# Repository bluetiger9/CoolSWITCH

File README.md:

# CoolSWITCH

**Project structure**
- CoolSWITH-Kicad - Kicad project: schematics + PCB
- CoolSwitch - Arduino project
- Smashing-Dashboard - Smashing demo dashboard
- MQTT-Grafana - Grafana demo dashboard
- coolSwitchClient.py - secure HTTP client
 
**License**: 
- code: MIT
- kicad design: CC BY-NC-SA

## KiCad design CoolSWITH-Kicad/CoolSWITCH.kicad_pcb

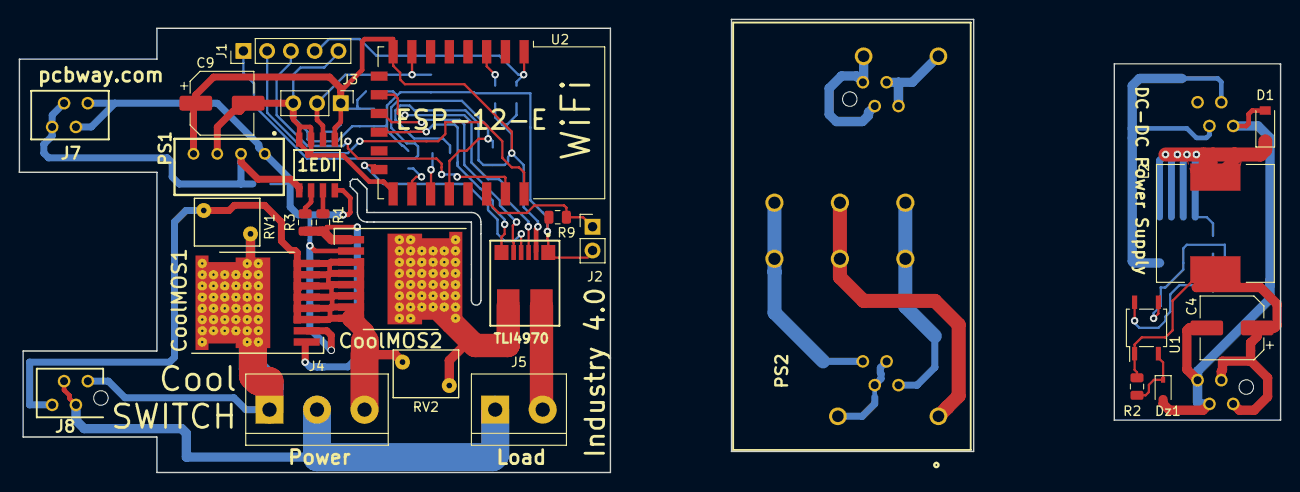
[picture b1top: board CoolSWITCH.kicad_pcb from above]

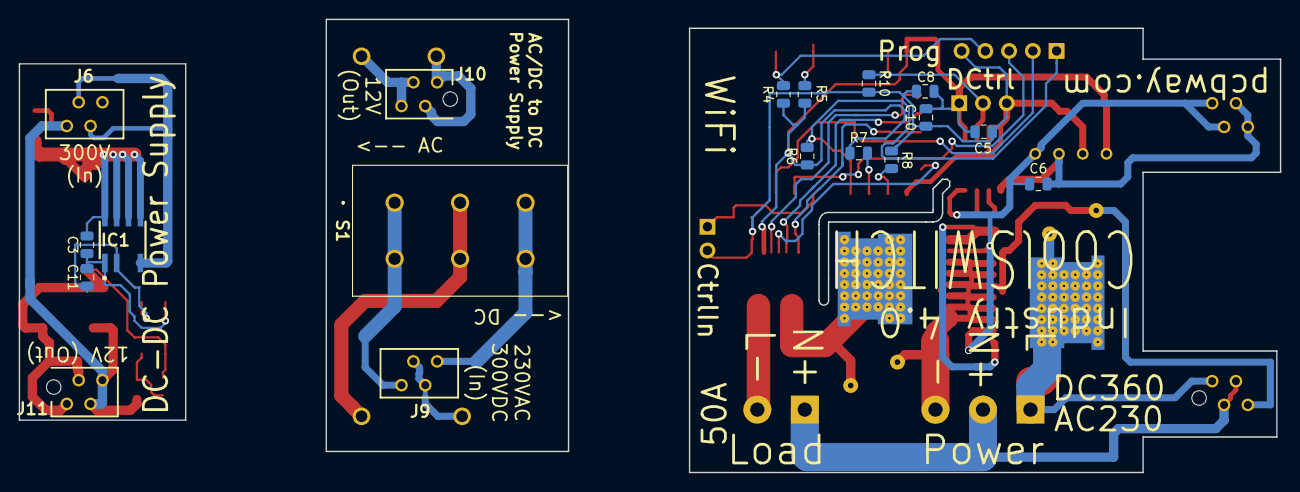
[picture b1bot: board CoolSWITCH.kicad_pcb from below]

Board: 2 copper layers, 134.9 x 48.5 mm, 44 parts (18 on the bottom side), 38 nets.

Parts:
1EDI: 1EDI20I12MFXUMA1; SOIC127P600X175-8N
C3: 0.1uF (25V); C_0805_2012Metric
C4: 220uF (16V); CP_Elec_6.3x7.7
C5, C8, C10: 100n; C_0805_2012Metric
C6: 1uF; C_0805_2012Metric
C9: 100u; CP_Elec_6.3x5.4
C11: 1nF (25V); C_0805_2012Metric
CoolMOS1, CoolMOS2: IPT60R028G7; Infineon_PG-HSOF-8-1_ThermalVias_fixed
D1: CD1408; D_SOD-123
Dz1: 11V; D_SOD-323
IC1: LNK3206D-TL; LNK3206D
J1: Prog; PinHeader_1x05_P2.54mm_Vertical
J2: CTRL_IN; PinHeader_1x02_P2.54mm_Vertical
J3: Direct_Ctrl; PinHeader_1x03_P2.54mm_Vertical
J4: POWER; TerminalBlock_bornier-3_P5.08mm
J5: LOAD; TerminalBlock_bornier-2_P5.08mm
J6, J9: PS_DC_IN; MicroMatch-215464-4
J7: PS_OUT; MicroMatch-215464-4
J8: PS_IN; MicroMatch-7-215079-4_1
J10: PS_DC_OUT; MicroMatch-7-215079-4_1
J11: PS_AC_OUT; MicroMatch-7-215079-4_1
L2: 1.2uH (400mA); L_12x12mm_H8mm
PS1: IE1203S; IE1224S-H
PS2: IRM-05-12; IRM-05-5
R1: 24 ohm (.5W); R_0805_2012Metric
R2: 1k (1%); R_0805_2012Metric
R3: 48 ohm (.5W); R_0805_2012Metric
R4, R5, R6, R7, R8, R9, R10: 10k; R_0805_2012Metric
RV1, RV2: 599V; RV_Disc_D7mm_W5.1mm_P5mm
S1: X22205CAAK
TLI4970: TLI4970D050T4XUMA1; PG-TISON-8-1
U1: PC817; SOP-4_3.8x4.1mm_P2.54mm
U2: ESP-12E; ESP-12E_2

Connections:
3.3V: 1EDI.1, C5.1, C8.1, C9.1, C10.2, J3.1, PS1.4, R4.1, R5.1, R6.1, R7.1, TLI4970.2, U2.8
12V: 1EDI.5, C6.1, C6.2, J7.1, J7.2, J7.3, J7.4, PS1.1, PS1.2
AC_IN_L: CoolMOS1.6, J4.1, J8.4, RV1.1
AC_IN_N: J4.2, J5.1, J8.2, J8.3
CRNT_CS: TLI4970.5, U2.11
CRNT_DOUT: TLI4970.3, U2.10
CRNT_OCD: TLI4970.6, U2.12
CRNT_SCLK: TLI4970.4, U2.14
CTRL_IN: J2.1, R9.1, U2.20
DC_IN_-: CoolMOS1.3, CoolMOS2.3, J4.3, J8.1, RV1.2, RV2.1
ESP_GPIO0: J1.1, R6.2, U2.18
ESP_RST: J1.4, R4.2, U2.1
ESP_RX: J1.3, U2.21
ESP_TX: J1.2, U2.22
GND: 1EDI.8, CoolMOS1.2, CoolMOS2.2
GND(logic): 1EDI.3, 1EDI.4, C5.2, C8.2, C9.2, C10.1, J1.5, J2.2, J3.3, PS1.3, R8.2, R9.2, R10.2, TLI4970.1, U2.15
Load: J5.2, TLI4970.8
Mosfet_En: 1EDI.2, J3.2, R10.1, U2.7
unnamed: C3.1, D1.1, IC1.5, IC1.6, IC1.7, IC1.8, L2.1
unnamed: C4.1, J11.3, J11.4, L2.2, R2.1, U1.1
unnamed: C4.2, D1.2, Dz1.2, J6.1, J11.1, J11.2
unnamed: C3.2, C11.1, IC1.1, U1.4
unnamed: C11.2, IC1.2, U1.3
unnamed: Dz1.1, R2.2, U1.2
unnamed: IC1.4, J6.2, J6.3
unnamed: 1EDI.6, R3.2
unnamed: 1EDI.7, R1.2
unnamed: CoolMOS2.6, RV2.2, TLI4970.7
unnamed: J9.1, S1.5, S1.6
unnamed: J9.2, J9.3, PS2.4
unnamed: J9.4, S1.1, S1.2
unnamed: J10.1, J10.2, PS2.2
unnamed: J10.3, J10.4, PS2.3
unnamed: PS2.1, S1.3, S1.4
unnamed: CoolMOS1.1, CoolMOS2.1, R1.1, R3.1
unnamed: R5.2, U2.3
unnamed: R7.2, U2.17
unnamed: R8.1, U2.16

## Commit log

2019-01-22 CoolSWITCH - add project files
2019-01-23 CoolSWITCH - implement soft switching, MQTT, Grafana dashboard, Smashing dashboard
2019-01-24 CoolSWITCH - security features
2019-01-26 CoolSWITCH - fix soft start / stop
2019-01-26 CoolSWITCH - add license file
2019-04-06 fix typo
2019-04-06 CoolSWITCH IOTA
2022-04-04 Bump rack from 2.0.6 to 2.0.9 in /Smashing-Dashboard
    Bumps [rack](https://github.com/rack/rack) from 2.0.6 to 2.0.9.
    - [Release notes](https://github.com/rack/rack/releases)
    - [Changelog](https://github.com/rack/rack/blob/main/CHANGELOG.md)
    - [Commits](https://github.com/rack/rack/compare/2.0.6...2.0.9)
    ---
    updated-dependencies:
2022-04-04 Bump minimist from 1.2.0 to 1.2.6 in /CoolSWITCH-IOTA
    Bumps [minimist](https://github.com/substack/minimist) from 1.2.0 to 1.2.6.
    - [Release notes](https://github.com/substack/minimist/releases)
    - [Commits](https://github.com/substack/minimist/compare/1.2.0...1.2.6)
    ---
    updated-dependencies:
    - dependency-name: minimist
2022-04-04 Bump addressable from 2.6.0 to 2.8.0 in /Smashing-Dashboard
    Bumps [addressable](https://github.com/sporkmonger/addressable) from 2.6.0 to 2.8.0.
    - [Release notes](https://github.com/sporkmonger/addressable/releases)
    - [Changelog](https://github.com/sporkmonger/addressable/blob/main/CHANGELOG.md)
    - [Commits](https://github.com/sporkmonger/addressable/compare/addressable-2.6.0...addressable-2.8.0)
    ---
    updated-dependencies:
2022-04-06 Bump node-fetch from 2.3.0 to 2.6.7 in /CoolSWITCH-IOTA
    Bumps [node-fetch](https://github.com/node-fetch/node-fetch) from 2.3.0 to 2.6.7.
    - [Release notes](https://github.com/node-fetch/node-fetch/releases)
    - [Commits](https://github.com/node-fetch/node-fetch/compare/v2.3.0...v2.6.7)
    ---
    updated-dependencies:
    - dependency-name: node-fetch
2022-06-05 Bump rack from 2.2.3 to 2.2.3.1 in /Smashing-Dashboard
    Bumps [rack](https://github.com/rack/rack) from 2.2.3 to 2.2.3.1.
    - [Release notes](https://github.com/rack/rack/releases)
    - [Changelog](https://github.com/rack/rack/blob/main/CHANGELOG.md)
    - [Commits](https://github.com/rack/rack/compare/2.2.3...2.2.3.1)
    ---
    updated-dependencies:
2022-06-05 Bump cross-fetch from 3.0.2 to 3.1.5 in /CoolSWITCH-IOTA
    Bumps [cross-fetch](https://github.com/lquixada/cross-fetch) from 3.0.2 to 3.1.5.
    - [Release notes](https://github.com/lquixada/cross-fetch/releases)
    - [Commits](https://github.com/lquixada/cross-fetch/compare/v3.0.2...v3.1.5)
    ---
    updated-dependencies:
    - dependency-name: cross-fetch
2022-12-01 Bump sinatra from 2.2.0 to 2.2.3 in /Smashing-Dashboard
    Bumps [sinatra](https://github.com/sinatra/sinatra) from 2.2.0 to 2.2.3.
    - [Release notes](https://github.com/sinatra/sinatra/releases)
    - [Changelog](https://github.com/sinatra/sinatra/blob/master/CHANGELOG.md)
    - [Commits](https://github.com/sinatra/sinatra/compare/v2.2.0...v2.2.3)
    ---
    updated-dependencies:
